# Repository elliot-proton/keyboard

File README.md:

# keyboard
A collection of scripts to create keyboard pcb files with Python and KiCAD

How to use:
1. create a keyboard layout at http://www.keyboard-layout-editor.com/
2. copy the layout to a file named `layout.txt` in the same directory as the scripts
3. run `net_from_kle.py` to create a KiCAD compatible netlist.
4. load this netlist in `PCBNEW` from within KiCAD
5. use the PCBNEW terminal to run `layout_from_kle.py` and refresh the board with `pcbnew.Refresh()`
6. route the board. Freerouting works well as an open source autorouter.

Limitations
- currently pro-micro only, so 64-key boards are the maximum.
- mounting holes or pcb mount stab holes must be done by hand.

# TODO:
- Create RGB net connections & decide on RGB control scheme
- Switch to microcontroller on board, instead of pro-micro
- Consolidate into a single program

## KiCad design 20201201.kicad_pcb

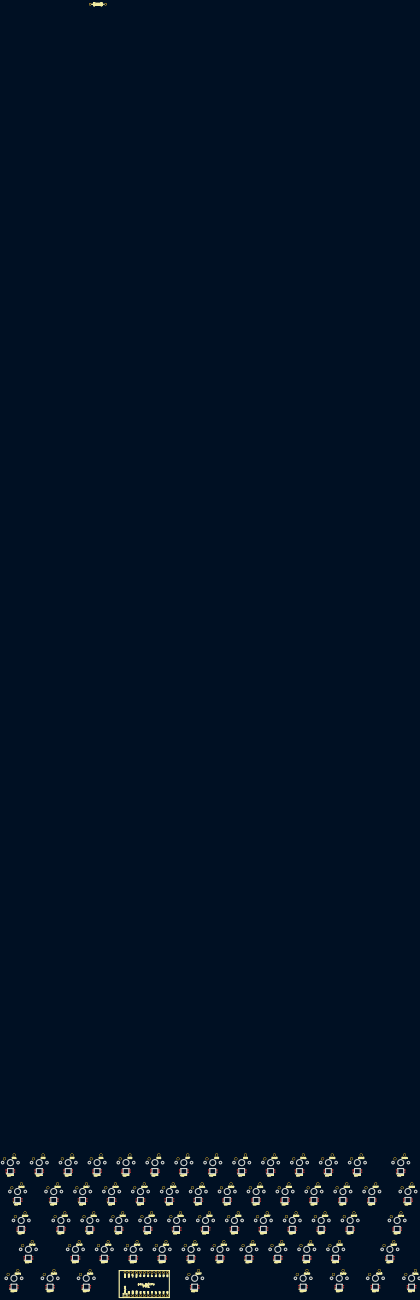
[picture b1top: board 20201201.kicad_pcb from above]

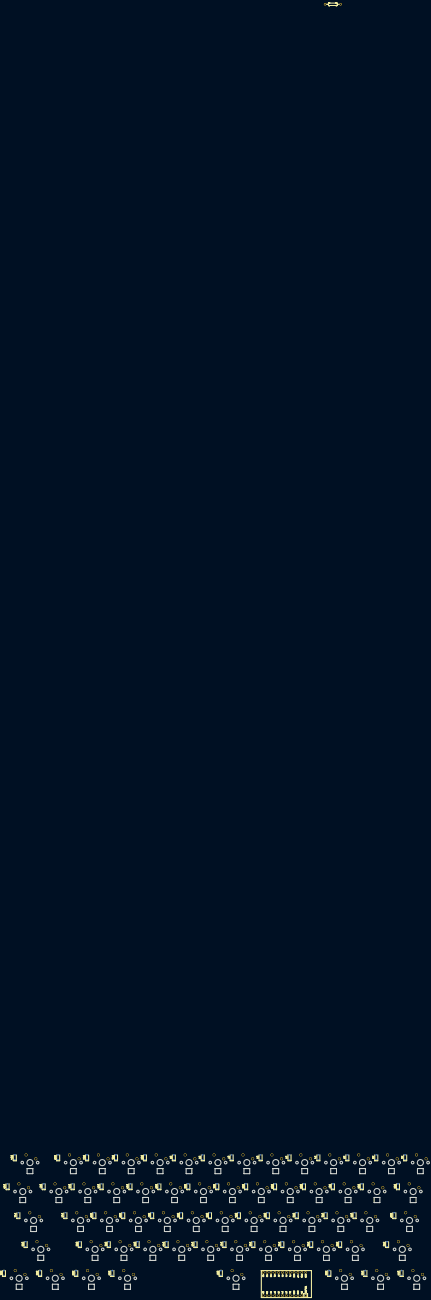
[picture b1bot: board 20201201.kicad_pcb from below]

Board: 2 copper layers, 124 parts (61 on the bottom side), 77 nets, no tracks yet.

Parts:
D1, D2, D3, D4, D5, D6, D7, D8, D9, D10, D11, D12, D13, D14, D15, D16, D17, D18, D19, D20, D21, D22, D23, D24, D25, D26, D27, D28, D29, D30, D31, D32, D33, D34, D35, D36, D37, D38, D39, D40, D41, D42, D43, D44, D45, D46, D47, D48, D49, D50, D51, D52, D53, D54, D55, D56, D57, D58, D59, D60, D61: diode; D_SOD-123
PM1: pro_micro; ArduinoProMicro
R1: resistor; Resistor
SW1, SW2, SW3, SW4, SW5, SW6, SW7, SW8, SW9, SW10, SW11, SW12, SW13, SW14, SW15, SW16, SW17, SW18, SW19, SW20, SW21, SW22, SW23, SW24, SW25, SW26, SW27, SW28, SW29, SW30, SW31, SW32, SW33, SW34, SW35, SW36, SW37, SW38, SW39, SW40, SW41, SW42, SW43, SW44, SW45, SW46, SW47, SW48, SW49, SW50, SW51, SW52, SW53, SW54, SW55, SW56, SW57, SW58, SW59, SW60, SW61: cherry_1u_rgb

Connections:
d_in0: D1.1, D9.1, D17.1, D25.1, D33.1, D41.1, D49.1, D57.1, PM1.13
d_in1: D2.1, D10.1, D18.1, D26.1, D34.1, D42.1, D50.1, D58.1, PM1.14
d_in2: D3.1, D11.1, D19.1, D27.1, D35.1, D43.1, D51.1, D59.1, PM1.15
d_in3: D4.1, D12.1, D20.1, D28.1, D36.1, D44.1, D52.1, D60.1, PM1.16
d_in4: D5.1, D13.1, D21.1, D29.1, D37.1, D45.1, D53.1, D61.1, PM1.17
d_in5: D6.1, D14.1, D22.1, D30.1, D38.1, D46.1, D54.1, PM1.18
d_in6: D7.1, D15.1, D23.1, D31.1, D39.1, D47.1, D55.1, PM1.19
d_in7: D8.1, D16.1, D24.1, D32.1, D40.1, D48.1, D56.1, PM1.20
row_out0: PM1.5, SW1.6, SW2.6, SW3.6, SW4.6, SW5.6, SW6.6, SW7.6, SW8.6
row_out1: PM1.6, SW9.6, SW10.6, SW11.6, SW12.6, SW13.6, SW14.6, SW15.6, SW16.6
row_out2: PM1.7, SW17.6, SW18.6, SW19.6, SW20.6, SW21.6, SW22.6, SW23.6, SW24.6
row_out3: PM1.8, SW25.6, SW26.6, SW27.6, SW28.6, SW29.6, SW30.6, SW31.6, SW32.6
row_out4: PM1.9, SW33.6, SW34.6, SW35.6, SW36.6, SW37.6, SW38.6, SW39.6, SW40.6
row_out5: PM1.10, SW41.6, SW42.6, SW43.6, SW44.6, SW45.6, SW46.6, SW47.6, SW48.6
row_out6: PM1.11, SW49.6, SW50.6, SW51.6, SW52.6, SW53.6, SW54.6, SW55.6, SW56.6
row_out7: PM1.12, SW57.6, SW58.6, SW59.6, SW60.6, SW61.6
sd00: D1.2, SW1.5
sd01: D2.2, SW2.5
sd02: D3.2, SW3.5
sd03: D4.2, SW4.5
sd04: D5.2, SW5.5
sd05: D6.2, SW6.5
sd06: D7.2, SW7.5
sd07: D8.2, SW8.5
sd10: D9.2, SW9.5
sd11: D10.2, SW10.5
sd12: D11.2, SW11.5
sd13: D12.2, SW12.5
sd14: D13.2, SW13.5
sd15: D14.2, SW14.5
sd16: D15.2, SW15.5
sd17: D16.2, SW16.5
sd20: D17.2, SW17.5
sd21: D18.2, SW18.5
sd22: D19.2, SW19.5
sd23: D20.2, SW20.5
sd24: D21.2, SW21.5
sd25: D22.2, SW22.5
sd26: D23.2, SW23.5
sd27: D24.2, SW24.5
sd30: D25.2, SW25.5
sd31: D26.2, SW26.5
sd32: D27.2, SW27.5
sd33: D28.2, SW28.5
sd34: D29.2, SW29.5
sd35: D30.2, SW30.5
sd36: D31.2, SW31.5
sd37: D32.2, SW32.5
sd40: D33.2, SW33.5
sd41: D34.2, SW34.5
sd42: D35.2, SW35.5
sd43: D36.2, SW36.5
sd44: D37.2, SW37.5
sd45: D38.2, SW38.5
sd46: D39.2, SW39.5
sd47: D40.2, SW40.5
sd50: D41.2, SW41.5
sd51: D42.2, SW42.5
sd52: D43.2, SW43.5
sd53: D44.2, SW44.5
sd54: D45.2, SW45.5
sd55: D46.2, SW46.5
sd56: D47.2, SW47.5
sd57: D48.2, SW48.5
sd60: D49.2, SW49.5
sd61: D50.2, SW50.5
sd62: D51.2, SW51.5
sd63: D52.2, SW52.5
sd64: D53.2, SW53.5
sd65: D54.2, SW54.5
sd66: D55.2, SW55.5
sd67: D56.2, SW56.5
sd70: D57.2, SW57.5
sd71: D58.2, SW58.5
sd72: D59.2, SW59.5
sd73: D60.2, SW60.5
sd74: D61.2, SW61.5

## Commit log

2020-12-03 initial upload
2020-12-03 key_testing.lib uploaded
